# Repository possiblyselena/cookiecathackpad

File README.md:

# Cookie Cat Hackpad! 

This is a project for Highway based on the YSWS hackpad! It's inspired by Steven Universe, one of my favourite shows growing up featuring 6 switches in a case that resembles cookie cat. The switches are mapped so I can copy and paste easier since my laptop is missing it's left control keycap. This is my first project, aside from solder for highway and I'm super excited to see what else I'll build!

# Schematic and PCB

# CAD

# Components
- 6x Cherry MX Switches
- 2x SK6812 MINI Leds
- 1x XIAO RP2040
- 6x Keycaps
- Custom 3D Printed Top Case
- Custom 3D Printed Bottom Case

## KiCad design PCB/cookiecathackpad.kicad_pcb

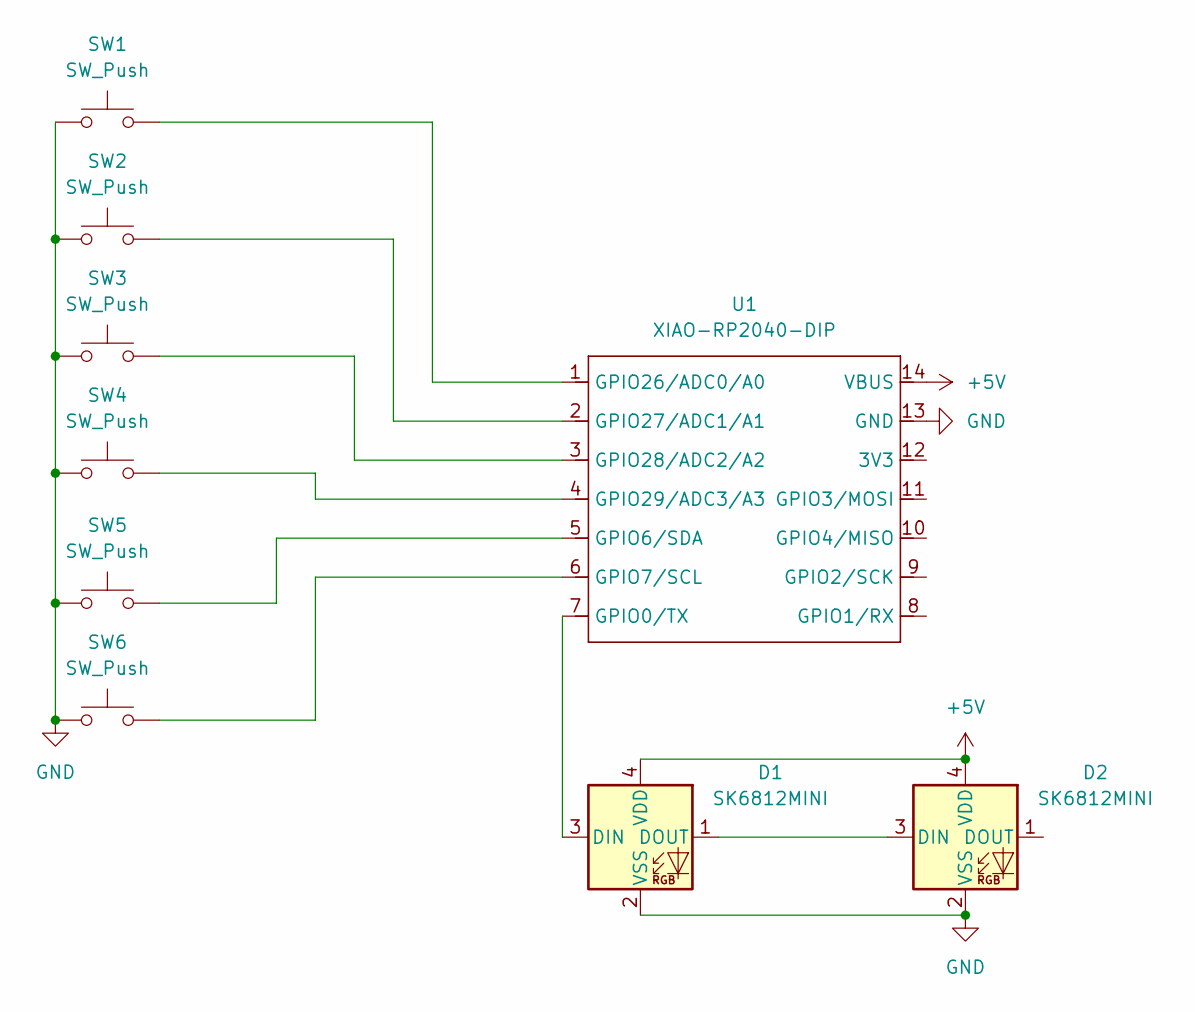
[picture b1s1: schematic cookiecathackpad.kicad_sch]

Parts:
D1, D2: SK6812MINI; LED_SK6812MINI_PLCC4_3.5x3.5mm_P1.75mm
SW1, SW2, SW3, SW4, SW5, SW6: SW_Push; SW_Cherry_MX_1.00u_PCB
U1: XIAO-RP2040-DIP

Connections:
+5V: D1.4 (VDD), D2.4 (VDD), U1.14 (VBUS)
GND: D1.2 (VSS), D2.2 (VSS), SW1.1, SW2.1, SW3.1, SW4.1, SW5.1, SW6.1, U1.13 (GND)
unnamed: D1.3 (DIN), U1.7 (GPIO0/TX)
unnamed: D1.1 (DOUT), D2.3 (DIN)
unnamed: SW5.2, U1.5 (GPIO6/SDA)
unnamed: SW6.2, U1.6 (GPIO7/SCL)
unnamed: SW1.2, U1.1 (GPIO26/ADC0/A0)
unnamed: SW2.2, U1.2 (GPIO27/ADC1/A1)
unnamed: SW3.2, U1.3 (GPIO28/ADC2/A2)
unnamed: SW4.2, U1.4 (GPIO29/ADC3/A3)

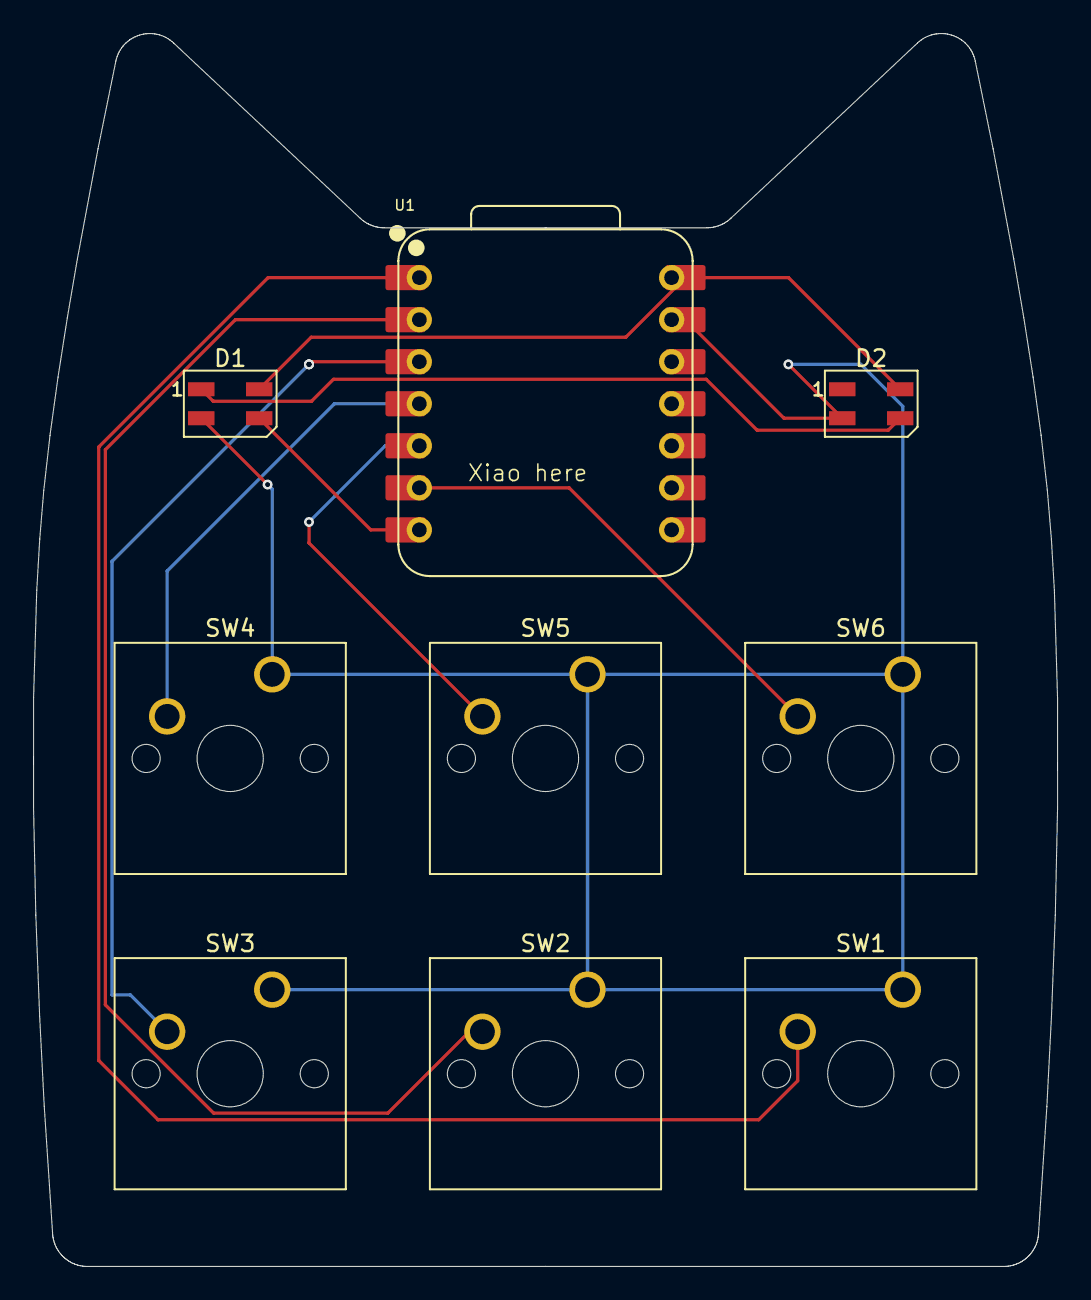
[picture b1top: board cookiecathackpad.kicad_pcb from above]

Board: 2 copper layers, 61.9 x 74.5 mm, 9 parts (0 on the bottom side), 10 nets.

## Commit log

2025-06-12 Create main.py
    firmware!
2025-06-14 Create PCB
